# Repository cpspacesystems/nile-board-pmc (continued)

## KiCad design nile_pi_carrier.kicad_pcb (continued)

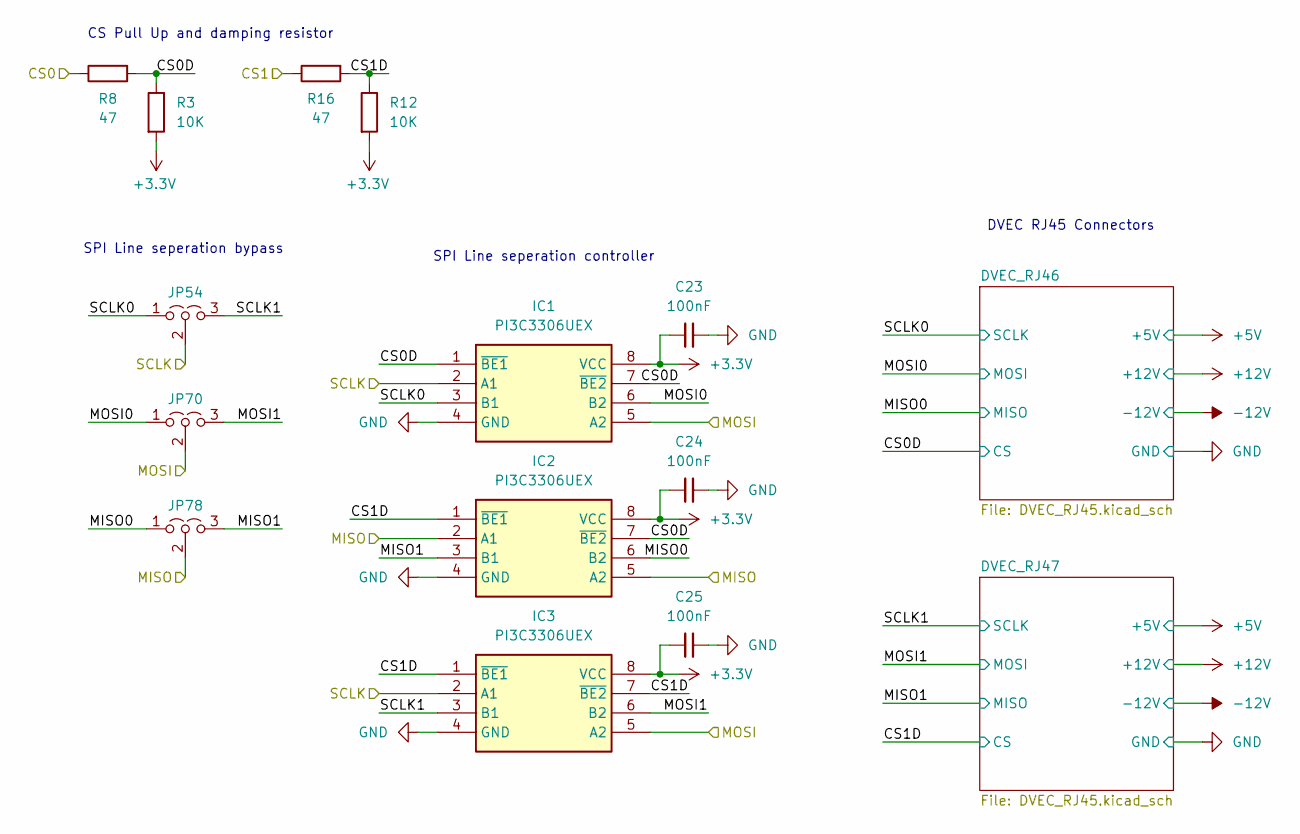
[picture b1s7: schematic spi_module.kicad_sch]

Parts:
C23, C24, C25: 100nF; C_0402_1005Metric
IC1, IC2, IC3: PI3C3306UEX; SOP65P490X110-8N; Manufacturer_Part_Number PI3C3306UEX; Mouser Part Number 729-PI3C3306UEX
JP54, JP70, JP78: SPI Iso Bypass; SolderJumper-3_P1.3mm_Open_Pad1.0x1.5mm_NumberLabels
R3, R12: 10K; R_0402_1005Metric_Pad0.72x0.64mm_HandSolder
R8, R16: 47; R_0402_1005Metric_Pad0.72x0.64mm_HandSolder

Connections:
+3.3V: C23.1, C24.1, C25.1, IC1.8 (VCC), IC2.8 (VCC), IC3.8 (VCC), R3.2, R12.2; also elsewhere on the board
/CS0: R8.1; also elsewhere on the board
/CS1: R16.1; also elsewhere on the board
/spi_bank/MISOA: IC2.2 (A1), IC2.5 (A2), JP78.2 (C); also elsewhere on the board
/spi_bank/MOSIA: IC1.5 (A2), IC3.5 (A2), JP70.2 (C); also elsewhere on the board
/spi_bank/SCLKA: IC1.2 (A1), IC3.2 (A1), JP54.2 (C); also elsewhere on the board
/spi_bank/SPI Module/CS0D: IC1.1 (~BE1), IC1.7 (~BE2), IC2.7 (~BE2), R3.1, R8.2; also elsewhere on the board
/spi_bank/SPI Module/CS1D: IC2.1 (~BE1), IC3.1 (~BE1), IC3.7 (~BE2), R12.1, R16.2; also elsewhere on the board
/spi_bank/SPI Module/MISO0: IC2.6 (B2), JP78.1 (A); also elsewhere on the board
/spi_bank/SPI Module/MISO1: IC2.3 (B1), JP78.3 (B); also elsewhere on the board
/spi_bank/SPI Module/MOSI0: IC1.6 (B2), JP70.1 (A); also elsewhere on the board
/spi_bank/SPI Module/MOSI1: IC3.6 (B2), JP70.3 (B); also elsewhere on the board
/spi_bank/SPI Module/SCLK0: IC1.3 (B1), JP54.1 (A); also elsewhere on the board
/spi_bank/SPI Module/SCLK1: IC3.3 (B1), JP54.3 (B); also elsewhere on the board
GND: C23.2, C24.2, C25.2, IC1.4 (GND), IC2.4 (GND), IC3.4 (GND); also elsewhere on the board

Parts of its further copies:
C26, C27, C28, C29, C30, C31, C32, C33, C34, C35, C36, C37, C38, C39, C40, C41, C42, C43, C44, C45, C46: 100nF; C_0402_1005Metric
IC4, IC5, IC6, IC7, IC8, IC9, IC10, IC11, IC12, IC13, IC14, IC15, IC16, IC17, IC18, IC19, IC20, IC21, IC22, IC23, IC24: PI3C3306UEX; SOP65P490X110-8N; Manufacturer_Part_Number PI3C3306UEX; Mouser Part Number 729-PI3C3306UEX
JP55, JP56, JP57, JP58, JP59, JP60, JP61, JP71, JP72, JP73, JP74, JP75, JP76, JP77, JP79, JP80, JP81, JP82, JP83, JP84, JP85: SPI Iso Bypass; SolderJumper-3_P1.3mm_Open_Pad1.0x1.5mm_NumberLabels
R40, R48, R56, R60, R68, R76, R80, R88, R96, R145, R147, R149, R151, R153: 10K; R_0402_1005Metric_Pad0.72x0.64mm_HandSolder
R44, R52, R57, R64, R72, R77, R84, R92, R144, R146, R148, R150, R152, R154: 47; R_0402_1005Metric_Pad0.72x0.64mm_HandSolder

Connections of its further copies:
+3.3V: C26.1, C27.1, C28.1, C29.1, C30.1, C31.1, C32.1, C33.1, C34.1, C35.1, C36.1, C37.1, C38.1, C39.1, C40.1, C41.1, C42.1, C43.1, C44.1, C45.1, C46.1, IC4.8 (VCC), IC5.8 (VCC), IC6.8 (VCC), IC7.8 (VCC), IC8.8 (VCC), IC9.8 (VCC), IC10.8 (VCC), IC11.8 (VCC), IC12.8 (VCC), IC13.8 (VCC), IC14.8 (VCC), IC15.8 (VCC), IC16.8 (VCC), IC17.8 (VCC), IC18.8 (VCC), IC19.8 (VCC), IC20.8 (VCC), IC21.8 (VCC), IC22.8 (VCC), IC23.8 (VCC), IC24.8 (VCC), R40.2, R48.2, R56.2, R60.2, R68.2, R76.2, R80.2, R88.2, R96.2, R145.2, R147.2, R149.2, R151.2, R153.2; also elsewhere on the board
/CS2: R44.1; also elsewhere on the board
/CS3: R52.1; also elsewhere on the board
/CS4: R57.1; also elsewhere on the board
/CS5: R64.1; also elsewhere on the board
/CS6: R72.1; also elsewhere on the board
/CS7: R77.1; also elsewhere on the board
/CS8: R84.1; also elsewhere on the board
/CS9: R92.1; also elsewhere on the board
/CS10: R144.1; also elsewhere on the board
/CS11: R146.1; also elsewhere on the board
/CS12: R148.1; also elsewhere on the board
/CS13: R150.1; also elsewhere on the board
/CS14: R152.1; also elsewhere on the board
/CS15: R154.1; also elsewhere on the board
/spi_bank/MISOA: IC5.2 (A1), IC5.5 (A2), IC8.2 (A1), IC8.5 (A2), IC11.2 (A1), IC11.5 (A2), JP79.2 (C), JP80.2 (C), JP81.2 (C); also elsewhere on the board
/spi_bank/MISOB: IC14.2 (A1), IC14.5 (A2), IC17.2 (A1), IC17.5 (A2), IC20.2 (A1), IC20.5 (A2), IC23.2 (A1), IC23.5 (A2), JP82.2 (C), JP83.2 (C), JP84.2 (C), JP85.2 (C); also elsewhere on the board
/spi_bank/MOSIA: IC4.5 (A2), IC6.5 (A2), IC7.5 (A2), IC9.5 (A2), IC10.5 (A2), IC12.5 (A2), JP71.2 (C), JP72.2 (C), JP73.2 (C); also elsewhere on the board
/spi_bank/MOSIB: IC13.5 (A2), IC15.5 (A2), IC16.5 (A2), IC18.5 (A2), IC19.5 (A2), IC21.5 (A2), IC22.5 (A2), IC24.5 (A2), JP74.2 (C), JP75.2 (C), JP76.2 (C), JP77.2 (C); also elsewhere on the board
/spi_bank/SCLKA: IC4.2 (A1), IC6.2 (A1), IC7.2 (A1), IC9.2 (A1), IC10.2 (A1), IC12.2 (A1), JP55.2 (C), JP56.2 (C), JP57.2 (C); also elsewhere on the board
/spi_bank/SCLKB: IC13.2 (A1), IC15.2 (A1), IC16.2 (A1), IC18.2 (A1), IC19.2 (A1), IC21.2 (A1), IC22.2 (A1), IC24.2 (A1), JP58.2 (C), JP59.2 (C), JP60.2 (C), JP61.2 (C); also elsewhere on the board
/spi_bank/SPI Module1/CS0D: IC4.1 (~BE1), IC4.7 (~BE2), IC5.7 (~BE2), R40.1, R44.2; also elsewhere on the board
/spi_bank/SPI Module1/CS1D: IC5.1 (~BE1), IC6.1 (~BE1), IC6.7 (~BE2), R48.1, R52.2; also elsewhere on the board
/spi_bank/SPI Module1/MISO0: IC5.6 (B2), JP79.1 (A); also elsewhere on the board
/spi_bank/SPI Module1/MISO1: IC5.3 (B1), JP79.3 (B); also elsewhere on the board
/spi_bank/SPI Module1/MOSI0: IC4.6 (B2), JP71.1 (A); also elsewhere on the board
/spi_bank/SPI Module1/MOSI1: IC6.6 (B2), JP71.3 (B); also elsewhere on the board
/spi_bank/SPI Module1/SCLK0: IC4.3 (B1), JP55.1 (A); also elsewhere on the board
/spi_bank/SPI Module1/SCLK1: IC6.3 (B1), JP55.3 (B); also elsewhere on the board
/spi_bank/SPI Module2/CS0D: IC7.1 (~BE1), IC7.7 (~BE2), IC8.7 (~BE2), R56.1, R57.2; also elsewhere on the board
/spi_bank/SPI Module2/CS1D: IC8.1 (~BE1), IC9.1 (~BE1), IC9.7 (~BE2), R60.1, R64.2; also elsewhere on the board
/spi_bank/SPI Module2/MISO0: IC8.6 (B2), JP80.1 (A); also elsewhere on the board
/spi_bank/SPI Module2/MISO1: IC8.3 (B1), JP80.3 (B); also elsewhere on the board
/spi_bank/SPI Module2/MOSI0: IC7.6 (B2), JP72.1 (A); also elsewhere on the board
/spi_bank/SPI Module2/MOSI1: IC9.6 (B2), JP72.3 (B); also elsewhere on the board
/spi_bank/SPI Module2/SCLK0: IC7.3 (B1), JP56.1 (A); also elsewhere on the board
/spi_bank/SPI Module2/SCLK1: IC9.3 (B1), JP56.3 (B); also elsewhere on the board
/spi_bank/SPI Module3/CS0D: IC10.1 (~BE1), IC10.7 (~BE2), IC11.7 (~BE2), R68.1, R72.2; also elsewhere on the board
/spi_bank/SPI Module3/CS1D: IC11.1 (~BE1), IC12.1 (~BE1), IC12.7 (~BE2), R76.1, R77.2; also elsewhere on the board
/spi_bank/SPI Module3/MISO0: IC11.6 (B2), JP81.1 (A); also elsewhere on the board
/spi_bank/SPI Module3/MISO1: IC11.3 (B1), JP81.3 (B); also elsewhere on the board
/spi_bank/SPI Module3/MOSI0: IC10.6 (B2), JP73.1 (A); also elsewhere on the board
/spi_bank/SPI Module3/MOSI1: IC12.6 (B2), JP73.3 (B); also elsewhere on the board
/spi_bank/SPI Module3/SCLK0: IC10.3 (B1), JP57.1 (A); also elsewhere on the board
/spi_bank/SPI Module3/SCLK1: IC12.3 (B1), JP57.3 (B); also elsewhere on the board
/spi_bank/SPI Module4/CS0D: IC13.1 (~BE1), IC13.7 (~BE2), IC14.7 (~BE2), R80.1, R84.2; also elsewhere on the board
/spi_bank/SPI Module4/CS1D: IC14.1 (~BE1), IC15.1 (~BE1), IC15.7 (~BE2), R88.1, R92.2; also elsewhere on the board
/spi_bank/SPI Module4/MISO0: IC14.6 (B2), JP82.1 (A); also elsewhere on the board
/spi_bank/SPI Module4/MISO1: IC14.3 (B1), JP82.3 (B); also elsewhere on the board
/spi_bank/SPI Module4/MOSI0: IC13.6 (B2), JP74.1 (A); also elsewhere on the board
/spi_bank/SPI Module4/MOSI1: IC15.6 (B2), JP74.3 (B); also elsewhere on the board
/spi_bank/SPI Module4/SCLK0: IC13.3 (B1), JP58.1 (A); also elsewhere on the board
/spi_bank/SPI Module4/SCLK1: IC15.3 (B1), JP58.3 (B); also elsewhere on the board
/spi_bank/SPI Module5/CS0D: IC16.1 (~BE1), IC16.7 (~BE2), IC17.7 (~BE2), R96.1, R144.2; also elsewhere on the board
/spi_bank/SPI Module5/CS1D: IC17.1 (~BE1), IC18.1 (~BE1), IC18.7 (~BE2), R145.1, R146.2; also elsewhere on the board
/spi_bank/SPI Module5/MISO0: IC17.6 (B2), JP83.1 (A); also elsewhere on the board
/spi_bank/SPI Module5/MISO1: IC17.3 (B1), JP83.3 (B); also elsewhere on the board
/spi_bank/SPI Module5/MOSI0: IC16.6 (B2), JP75.1 (A); also elsewhere on the board
/spi_bank/SPI Module5/MOSI1: IC18.6 (B2), JP75.3 (B); also elsewhere on the board
/spi_bank/SPI Module5/SCLK0: IC16.3 (B1), JP59.1 (A); also elsewhere on the board
/spi_bank/SPI Module5/SCLK1: IC18.3 (B1), JP59.3 (B); also elsewhere on the board
/spi_bank/SPI Module6/CS0D: IC19.1 (~BE1), IC19.7 (~BE2), IC20.7 (~BE2), R147.1, R148.2; also elsewhere on the board
/spi_bank/SPI Module6/CS1D: IC20.1 (~BE1), IC21.1 (~BE1), IC21.7 (~BE2), R149.1, R150.2; also elsewhere on the board
/spi_bank/SPI Module6/MISO0: IC20.6 (B2), JP84.1 (A); also elsewhere on the board
/spi_bank/SPI Module6/MISO1: IC20.3 (B1), JP84.3 (B); also elsewhere on the board
/spi_bank/SPI Module6/MOSI0: IC19.6 (B2), JP76.1 (A); also elsewhere on the board
/spi_bank/SPI Module6/MOSI1: IC21.6 (B2), JP76.3 (B); also elsewhere on the board
/spi_bank/SPI Module6/SCLK0: IC19.3 (B1), JP60.1 (A); also elsewhere on the board
/spi_bank/SPI Module6/SCLK1: IC21.3 (B1), JP60.3 (B); also elsewhere on the board
/spi_bank/SPI Module7/CS0D: IC22.1 (~BE1), IC22.7 (~BE2), IC23.7 (~BE2), R151.1, R152.2; also elsewhere on the board
/spi_bank/SPI Module7/CS1D: IC23.1 (~BE1), IC24.1 (~BE1), IC24.7 (~BE2), R153.1, R154.2; also elsewhere on the board
/spi_bank/SPI Module7/MISO0: IC23.6 (B2), JP85.1 (A); also elsewhere on the board
/spi_bank/SPI Module7/MISO1: IC23.3 (B1), JP85.3 (B); also elsewhere on the board
/spi_bank/SPI Module7/MOSI0: IC22.6 (B2), JP77.1 (A); also elsewhere on the board
/spi_bank/SPI Module7/MOSI1: IC24.6 (B2), JP77.3 (B); also elsewhere on the board
/spi_bank/SPI Module7/SCLK0: IC22.3 (B1), JP61.1 (A); also elsewhere on the board
/spi_bank/SPI Module7/SCLK1: IC24.3 (B1), JP61.3 (B); also elsewhere on the board
GND: C26.2, C27.2, C28.2, C29.2, C30.2, C31.2, C32.2, C33.2, C34.2, C35.2, C36.2, C37.2, C38.2, C39.2, C40.2, C41.2, C42.2, C43.2, C44.2, C45.2, C46.2, IC4.4 (GND), IC5.4 (GND), IC6.4 (GND), IC7.4 (GND), IC8.4 (GND), IC9.4 (GND), IC10.4 (GND), IC11.4 (GND), IC12.4 (GND), IC13.4 (GND), IC14.4 (GND), IC15.4 (GND), IC16.4 (GND), IC17.4 (GND), IC18.4 (GND), IC19.4 (GND), IC20.4 (GND), IC21.4 (GND), IC22.4 (GND), IC23.4 (GND), IC24.4 (GND); also elsewhere on the board

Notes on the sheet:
DVEC RJ45 Connectors
SPI Line seperation bypass
SPI Line seperation controller
CS Pull Up and damping resistor

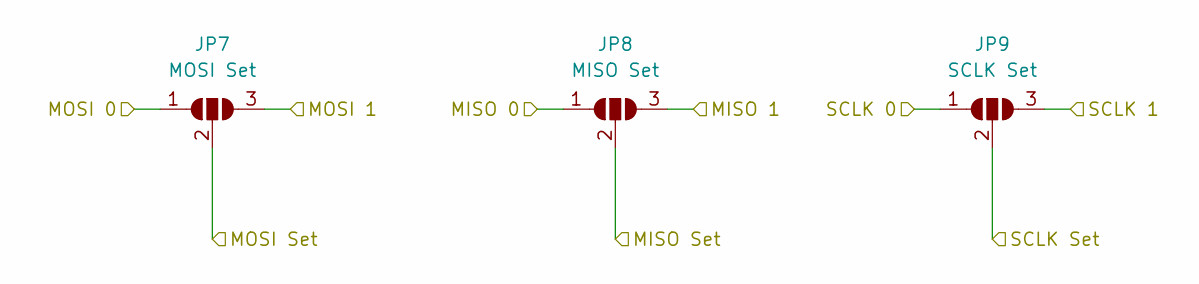
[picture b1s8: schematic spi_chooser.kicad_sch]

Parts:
JP7: MOSI Set; SolderJumper-3_P1.3mm_Open_Pad1.0x1.5mm_NumberLabels
JP8: MISO Set; SolderJumper-3_P1.3mm_Open_Pad1.0x1.5mm_NumberLabels
JP9: SCLK Set; SolderJumper-3_P1.3mm_Open_Pad1.0x1.5mm_NumberLabels

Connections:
/spi_bank/MISOA: JP8.2 (C); also elsewhere on the board
/spi_bank/MISOD0: JP8.1 (A); also elsewhere on the board
/spi_bank/MISOD1: JP8.3 (B); also elsewhere on the board
/spi_bank/MOSIA: JP7.2 (C); also elsewhere on the board
/spi_bank/MOSID0: JP7.1 (A); also elsewhere on the board
/spi_bank/MOSID1: JP7.3 (B); also elsewhere on the board
/spi_bank/SCLKA: JP9.2 (C); also elsewhere on the board
/spi_bank/SCLKD0: JP9.1 (A); also elsewhere on the board
/spi_bank/SCLKD1: JP9.3 (B); also elsewhere on the board

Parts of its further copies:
JP10: MOSI Set; SolderJumper-3_P1.3mm_Open_Pad1.0x1.5mm_NumberLabels
JP11: MISO Set; SolderJumper-3_P1.3mm_Open_Pad1.0x1.5mm_NumberLabels
JP12: SCLK Set; SolderJumper-3_P1.3mm_Open_Pad1.0x1.5mm_NumberLabels

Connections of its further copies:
/spi_bank/MISOB: JP11.2 (C); also elsewhere on the board
/spi_bank/MISOD0: JP11.1 (A); also elsewhere on the board
/spi_bank/MISOD1: JP11.3 (B); also elsewhere on the board
/spi_bank/MOSIB: JP10.2 (C); also elsewhere on the board
/spi_bank/MOSID0: JP10.1 (A); also elsewhere on the board
/spi_bank/MOSID1: JP10.3 (B); also elsewhere on the board
/spi_bank/SCLKB: JP12.2 (C); also elsewhere on the board
/spi_bank/SCLKD0: JP12.1 (A); also elsewhere on the board
/spi_bank/SCLKD1: JP12.3 (B); also elsewhere on the board

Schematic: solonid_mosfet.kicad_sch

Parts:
D1: SMF28A; D_SOD-123F
D25: LED; D_0603_1608Metric_Pad1.05x0.95mm_HandSolder
F2: PF 100mA; Fuse_1206_3216Metric_Pad1.42x1.75mm_HandSolder
Q1: BSS84; SOT-23
Q2: 2SK3018; SOT-323_SC-70
R1, R155: 27K; R_0402_1005Metric_Pad0.72x0.64mm_HandSolder
R2: 280; R_0402_1005Metric_Pad0.72x0.64mm_HandSolder
R85: 5.1K; R_0805_2012Metric_Pad1.20x1.40mm_HandSolder
R120: 10K; R_0402_1005Metric_Pad0.72x0.64mm_HandSolder

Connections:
/Solonid Bank Controller/DSUB 1: D1.1 (A1), F2.2, R85.1; also elsewhere on the board
/Solonid Bank Controller/S1 A: R2.2, R120.2; also elsewhere on the board
GND: D1.2 (A2), D25.1 (K), Q2.2 (S), R120.1; also elsewhere on the board
unnamed: D25.2 (A), R85.2
unnamed: F2.1, Q1.3 (D)
unnamed: Q1.1 (G), R1.2, R155.1
unnamed: Q2.3 (D), R155.2
unnamed: Q2.1 (G), R2.1
VBUS: Q1.2 (S), R1.1; also elsewhere on the board

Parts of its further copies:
D2, D3, D4, D5, D6, D7, D8, D9, D10, D11, D12, D13, D14, D15, D16, D17, D18, D19, D20, D21, D22, D23, D24: SMF28A; D_SOD-123F
D26, D27, D28, D29, D30, D31, D32, D33, D34, D35, D36, D37, D38, D39, D40, D41, D42, D43, D44, D45, D46, D47, D48: LED; D_0603_1608Metric_Pad1.05x0.95mm_HandSolder
F3, F4, F5, F6, F7, F8, F9, F10, F11, F12, F13, F14, F15, F16, F17, F18, F19, F20, F21, F22, F23, F24, F25: PF 100mA; Fuse_1206_3216Metric_Pad1.42x1.75mm_HandSolder
Q3, Q5, Q7, Q9, Q11, Q13, Q15, Q17, Q19, Q21, Q23, Q25, Q27, Q29, Q31, Q33, Q35, Q37, Q39, Q41, Q43, Q45, Q47: 2SK3018; SOT-323_SC-70
Q4, Q6, Q8, Q10, Q12, Q14, Q16, Q18, Q20, Q22, Q24, Q26, Q28, Q30, Q32, Q34, Q36, Q38, Q40, Q42, Q44, Q46, Q48: BSS84; SOT-23
R6, R10, R14, R18, R22, R26, R30, R34, R38, R42, R46, R50, R54, R58, R62, R66, R70, R74, R78, R82, R86, R90, R94: 280; R_0402_1005Metric_Pad0.72x0.64mm_HandSolder
R7, R11, R15, R19, R23, R27, R31, R35, R39, R43, R47, R51, R55, R59, R63, R67, R71, R75, R79, R83, R87, R91, R95, R156, R157, R158, R159, R161, R162, R163, R164, R165, R166, R167, R168, R169, R170, R171, R172, R173, R174, R175, R176, R177, R178, R179: 27K; R_0402_1005Metric_Pad0.72x0.64mm_HandSolder
R89, R93, R99, R100, R101, R102, R103, R104, R105, R106, R107, R108, R109, R110, R111, R112, R113, R114, R115, R116, R117, R118, R119: 5.1K; R_0805_2012Metric_Pad1.20x1.40mm_HandSolder
R121, R122, R123, R124, R125, R126, R127, R128, R129, R130, R131, R132, R133, R134, R135, R136, R137, R138, R139, R140, R141, R142, R143: 10K; R_0402_1005Metric_Pad0.72x0.64mm_HandSolder

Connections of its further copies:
/Solonid Bank Controller/DSUB 2: D3.1 (A1), F4.2, R93.1; also elsewhere on the board
/Solonid Bank Controller/DSUB 3: D5.1 (A1), F6.2, R100.1; also elsewhere on the board
/Solonid Bank Controller/DSUB 4: D7.1 (A1), F8.2, R102.1; also elsewhere on the board
/Solonid Bank Controller/DSUB 5: D9.1 (A1), F10.2, R104.1; also elsewhere on the board
/Solonid Bank Controller/DSUB 6: D11.1 (A1), F12.2, R106.1; also elsewhere on the board
/Solonid Bank Controller/DSUB 7: D13.1 (A1), F14.2, R108.1; also elsewhere on the board
/Solonid Bank Controller/DSUB 8: D15.1 (A1), F16.2, R110.1; also elsewhere on the board
/Solonid Bank Controller/DSUB 9: D17.1 (A1), F18.2, R112.1; also elsewhere on the board
/Solonid Bank Controller/DSUB 10: D19.1 (A1), F20.2, R114.1; also elsewhere on the board
/Solonid Bank Controller/DSUB 11: D21.1 (A1), F22.2, R116.1; also elsewhere on the board
/Solonid Bank Controller/DSUB 12: D23.1 (A1), F24.2, R118.1; also elsewhere on the board
/Solonid Bank Controller/DSUB 14: D2.1 (A1), F3.2, R89.1; also elsewhere on the board
/Solonid Bank Controller/DSUB 15: D4.1 (A1), F5.2, R99.1; also elsewhere on the board
/Solonid Bank Controller/DSUB 16: D6.1 (A1), F7.2, R101.1; also elsewhere on the board
/Solonid Bank Controller/DSUB 17: D8.1 (A1), F9.2, R103.1; also elsewhere on the board
/Solonid Bank Controller/DSUB 18: D10.1 (A1), F11.2, R105.1; also elsewhere on the board
/Solonid Bank Controller/DSUB 19: D12.1 (A1), F13.2, R107.1; also elsewhere on the board
/Solonid Bank Controller/DSUB 20: D14.1 (A1), F15.2, R109.1; also elsewhere on the board
/Solonid Bank Controller/DSUB 21: D16.1 (A1), F17.2, R111.1; also elsewhere on the board
/Solonid Bank Controller/DSUB 22: D18.1 (A1), F19.2, R113.1; also elsewhere on the board
/Solonid Bank Controller/DSUB 23: D20.1 (A1), F21.2, R115.1; also elsewhere on the board
/Solonid Bank Controller/DSUB 24: D22.1 (A1), F23.2, R117.1; also elsewhere on the board
/Solonid Bank Controller/DSUB 25: D24.1 (A1), F25.2, R119.1; also elsewhere on the board
/Solonid Bank Controller/S1 B: R6.2, R121.2; also elsewhere on the board
/Solonid Bank Controller/S2 A: R10.2, R122.2; also elsewhere on the board
/Solonid Bank Controller/S2 B: R14.2, R123.2; also elsewhere on the board
/Solonid Bank Controller/S3 A: R18.2, R124.2; also elsewhere on the board
/Solonid Bank Controller/S3 B: R22.2, R125.2; also elsewhere on the board
/Solonid Bank Controller/S4 A: R26.2, R126.2; also elsewhere on the board
/Solonid Bank Controller/S4 B: R30.2, R127.2; also elsewhere on the board
/Solonid Bank Controller/S5 A: R34.2, R128.2; also elsewhere on the board
/Solonid Bank Controller/S5 B: R38.2, R129.2; also elsewhere on the board
/Solonid Bank Controller/S6 A: R42.2, R130.2; also elsewhere on the board
/Solonid Bank Controller/S6 B: R46.2, R131.2; also elsewhere on the board
/Solonid Bank Controller/S7 A: R50.2, R132.2; also elsewhere on the board
/Solonid Bank Controller/S7 B: R54.2, R133.2; also elsewhere on the board
/Solonid Bank Controller/S8 A: R58.2, R134.2; also elsewhere on the board
/Solonid Bank Controller/S8 B: R62.2, R135.2; also elsewhere on the board
/Solonid Bank Controller/S9 A: R66.2, R136.2; also elsewhere on the board
/Solonid Bank Controller/S9 B: R70.2, R137.2; also elsewhere on the board
/Solonid Bank Controller/S10 A: R74.2, R138.2; also elsewhere on the board
/Solonid Bank Controller/S10 B: R78.2, R139.2; also elsewhere on the board
/Solonid Bank Controller/S11 A: R82.2, R140.2; also elsewhere on the board
/Solonid Bank Controller/S11 B: R86.2, R141.2; also elsewhere on the board
/Solonid Bank Controller/S12 A: R90.2, R142.2; also elsewhere on the board
/Solonid Bank Controller/S12 B: R94.2, R143.2; also elsewhere on the board
GND: D2.2 (A2), D3.2 (A2), D4.2 (A2), D5.2 (A2), D6.2 (A2), D7.2 (A2), D8.2 (A2), D9.2 (A2), D10.2 (A2), D11.2 (A2), D12.2 (A2), D13.2 (A2), D14.2 (A2), D15.2 (A2), D16.2 (A2), D17.2 (A2), D18.2 (A2), D19.2 (A2), D20.2 (A2), D21.2 (A2), D22.2 (A2), D23.2 (A2), D24.2 (A2), D26.1 (K), D27.1 (K), D28.1 (K), D29.1 (K), D30.1 (K), D31.1 (K), D32.1 (K), D33.1 (K), D34.1 (K), D35.1 (K), D36.1 (K), D37.1 (K), D38.1 (K), D39.1 (K), D40.1 (K), D41.1 (K), D42.1 (K), D43.1 (K), D44.1 (K), D45.1 (K), D46.1 (K), D47.1 (K), D48.1 (K), Q3.2 (S), Q5.2 (S), Q7.2 (S), Q9.2 (S), Q11.2 (S), Q13.2 (S), Q15.2 (S), Q17.2 (S), Q19.2 (S), Q21.2 (S), Q23.2 (S), Q25.2 (S), Q27.2 (S), Q29.2 (S), Q31.2 (S), Q33.2 (S), Q35.2 (S), Q37.2 (S), Q39.2 (S), Q41.2 (S), Q43.2 (S), Q45.2 (S), Q47.2 (S), R121.1, R122.1, R123.1, R124.1, R125.1, R126.1, R127.1, R128.1, R129.1, R130.1, R131.1, R132.1, R133.1, R134.1, R135.1, R136.1, R137.1, R138.1, R139.1, R140.1, R141.1, R142.1, R143.1; also elsewhere on the board
unnamed: D26.2 (A), R89.2
unnamed: D27.2 (A), R93.2
unnamed: D28.2 (A), R99.2
unnamed: D29.2 (A), R100.2
unnamed: D30.2 (A), R101.2
unnamed: D31.2 (A), R102.2
unnamed: D32.2 (A), R103.2
unnamed: D33.2 (A), R104.2
unnamed: D34.2 (A), R105.2
unnamed: D35.2 (A), R106.2
unnamed: D36.2 (A), R107.2
unnamed: D37.2 (A), R108.2
unnamed: D38.2 (A), R109.2
unnamed: D39.2 (A), R110.2
unnamed: D40.2 (A), R111.2
unnamed: D41.2 (A), R112.2
unnamed: D42.2 (A), R113.2
unnamed: D43.2 (A), R114.2
unnamed: D44.2 (A), R115.2
unnamed: D45.2 (A), R116.2
unnamed: D46.2 (A), R117.2
unnamed: D47.2 (A), R118.2
unnamed: D48.2 (A), R119.2
unnamed: Q3.3 (D), R156.2
unnamed: Q3.1 (G), R6.1
unnamed: F3.1, Q4.3 (D)
unnamed: Q4.1 (G), R7.2, R156.1
unnamed: Q5.3 (D), R157.2
unnamed: Q5.1 (G), R10.1
unnamed: F4.1, Q6.3 (D)
unnamed: Q6.1 (G), R11.2, R157.1
unnamed: Q7.3 (D), R158.2
unnamed: Q7.1 (G), R14.1
unnamed: F5.1, Q8.3 (D)
unnamed: Q8.1 (G), R15.2, R158.1
unnamed: Q9.3 (D), R159.2
unnamed: Q9.1 (G), R18.1
unnamed: F6.1, Q10.3 (D)
unnamed: Q10.1 (G), R19.2, R159.1
unnamed: Q11.3 (D), R161.2
unnamed: Q11.1 (G), R22.1
unnamed: F7.1, Q12.3 (D)
unnamed: Q12.1 (G), R23.2, R161.1
unnamed: Q13.3 (D), R162.2
unnamed: Q13.1 (G), R26.1
unnamed: F8.1, Q14.3 (D)
unnamed: Q14.1 (G), R27.2, R162.1
unnamed: Q15.3 (D), R163.2
unnamed: Q15.1 (G), R30.1
unnamed: F9.1, Q16.3 (D)
unnamed: Q16.1 (G), R31.2, R163.1
unnamed: Q17.3 (D), R164.2
unnamed: Q17.1 (G), R34.1
unnamed: F10.1, Q18.3 (D)
unnamed: Q18.1 (G), R35.2, R164.1
unnamed: Q19.3 (D), R165.2
unnamed: Q19.1 (G), R38.1
unnamed: F11.1, Q20.3 (D)
unnamed: Q20.1 (G), R39.2, R165.1
unnamed: Q21.3 (D), R166.2
unnamed: Q21.1 (G), R42.1
unnamed: F12.1, Q22.3 (D)
unnamed: Q22.1 (G), R43.2, R166.1
unnamed: Q23.3 (D), R167.2
unnamed: Q23.1 (G), R46.1
unnamed: F13.1, Q24.3 (D)
unnamed: Q24.1 (G), R47.2, R167.1
unnamed: Q25.3 (D), R168.2
unnamed: Q25.1 (G), R50.1
unnamed: F14.1, Q26.3 (D)
unnamed: Q26.1 (G), R51.2, R168.1
unnamed: Q27.3 (D), R169.2
unnamed: Q27.1 (G), R54.1
unnamed: F15.1, Q28.3 (D)
unnamed: Q28.1 (G), R55.2, R169.1
unnamed: Q29.3 (D), R170.2
unnamed: Q29.1 (G), R58.1
unnamed: F16.1, Q30.3 (D)
unnamed: Q30.1 (G), R59.2, R170.1
unnamed: Q31.3 (D), R171.2
unnamed: Q31.1 (G), R62.1
unnamed: F17.1, Q32.3 (D)
unnamed: Q32.1 (G), R63.2, R171.1
unnamed: Q33.3 (D), R172.2
unnamed: Q33.1 (G), R66.1
unnamed: F18.1, Q34.3 (D)
unnamed: Q34.1 (G), R67.2, R172.1
unnamed: Q35.3 (D), R173.2
unnamed: Q35.1 (G), R70.1
unnamed: F19.1, Q36.3 (D)
unnamed: Q36.1 (G), R71.2, R173.1
unnamed: Q37.3 (D), R174.2
unnamed: Q37.1 (G), R74.1
unnamed: F20.1, Q38.3 (D)
unnamed: Q38.1 (G), R75.2, R174.1
unnamed: Q39.3 (D), R175.2
unnamed: Q39.1 (G), R78.1
unnamed: F21.1, Q40.3 (D)
unnamed: Q40.1 (G), R79.2, R175.1
unnamed: Q41.3 (D), R176.2
unnamed: Q41.1 (G), R82.1
unnamed: F22.1, Q42.3 (D)
unnamed: Q42.1 (G), R83.2, R176.1
unnamed: Q43.3 (D), R177.2
unnamed: Q43.1 (G), R86.1
unnamed: F23.1, Q44.3 (D)
unnamed: Q44.1 (G), R87.2, R177.1
unnamed: Q45.3 (D), R178.2
unnamed: Q45.1 (G), R90.1
unnamed: F24.1, Q46.3 (D)
unnamed: Q46.1 (G), R91.2, R178.1
unnamed: Q47.3 (D), R179.2
unnamed: Q47.1 (G), R94.1
unnamed: F25.1, Q48.3 (D)
unnamed: Q48.1 (G), R95.2, R179.1
VBUS: Q4.2 (S), Q6.2 (S), Q8.2 (S), Q10.2 (S), Q12.2 (S), Q14.2 (S), Q16.2 (S), Q18.2 (S), Q20.2 (S), Q22.2 (S), Q24.2 (S), Q26.2 (S), Q28.2 (S), Q30.2 (S), Q32.2 (S), Q34.2 (S), Q36.2 (S), Q38.2 (S), Q40.2 (S), Q42.2 (S), Q44.2 (S), Q46.2 (S), Q48.2 (S), R7.1, R11.1, R15.1, R19.1, R23.1, R27.1, R31.1, R35.1, R39.1, R43.1, R47.1, R51.1, R55.1, R59.1, R63.1, R67.1, R71.1, R75.1, R79.1, R83.1, R87.1, R91.1, R95.1; also elsewhere on the board

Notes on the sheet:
Half of VBUS
Ensure there is a close ground connection to SMF28A To minminize ground loop for return current

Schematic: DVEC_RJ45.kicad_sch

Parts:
J11: RJ45; RJ45-TH_RJ-804-1-6 Yellow

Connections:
+5V: J11.5; also elsewhere on the board
+12V: J11.8; also elsewhere on the board
-12V: J11.7; also elsewhere on the board
/spi_bank/SPI Module/CS0D: J11.2; also elsewhere on the board
/spi_bank/SPI Module/MISO0: J11.6; also elsewhere on the board
/spi_bank/SPI Module/MOSI0: J11.3; also elsewhere on the board
/spi_bank/SPI Module/SCLK0: J11.1; also elsewhere on the board
GND: J11.4; also elsewhere on the board

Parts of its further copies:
J12, J13, J14, J15, J21, J22, J23, J24, J25, J26, J27, J28, J29, J30, J31: RJ45; RJ45-TH_RJ-804-1-6 Yellow

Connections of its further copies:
+5V: J12.5, J13.5, J14.5, J15.5, J21.5, J22.5, J23.5, J24.5, J25.5, J26.5, J27.5, J28.5, J29.5, J30.5, J31.5; also elsewhere on the board
+12V: J12.8, J13.8, J14.8, J15.8, J21.8, J22.8, J23.8, J24.8, J25.8, J26.8, J27.8, J28.8, J29.8, J30.8, J31.8; also elsewhere on the board
-12V: J12.7, J13.7, J14.7, J15.7, J21.7, J22.7, J23.7, J24.7, J25.7, J26.7, J27.7, J28.7, J29.7, J30.7, J31.7; also elsewhere on the board
/spi_bank/SPI Module1/CS0D: J13.2; also elsewhere on the board
/spi_bank/SPI Module1/CS1D: J14.2; also elsewhere on the board
/spi_bank/SPI Module1/MISO0: J13.6; also elsewhere on the board
/spi_bank/SPI Module1/MISO1: J14.6; also elsewhere on the board
/spi_bank/SPI Module1/MOSI0: J13.3; also elsewhere on the board
/spi_bank/SPI Module1/MOSI1: J14.3; also elsewhere on the board
/spi_bank/SPI Module1/SCLK0: J13.1; also elsewhere on the board
/spi_bank/SPI Module1/SCLK1: J14.1; also elsewhere on the board
/spi_bank/SPI Module2/CS0D: J15.2; also elsewhere on the board
/spi_bank/SPI Module2/CS1D: J21.2; also elsewhere on the board
/spi_bank/SPI Module2/MISO0: J15.6; also elsewhere on the board
/spi_bank/SPI Module2/MISO1: J21.6; also elsewhere on the board
/spi_bank/SPI Module2/MOSI0: J15.3; also elsewhere on the board
/spi_bank/SPI Module2/MOSI1: J21.3; also elsewhere on the board
/spi_bank/SPI Module2/SCLK0: J15.1; also elsewhere on the board
/spi_bank/SPI Module2/SCLK1: J21.1; also elsewhere on the board
/spi_bank/SPI Module3/CS0D: J22.2; also elsewhere on the board
/spi_bank/SPI Module3/CS1D: J23.2; also elsewhere on the board
/spi_bank/SPI Module3/MISO0: J22.6; also elsewhere on the board
/spi_bank/SPI Module3/MISO1: J23.6; also elsewhere on the board
/spi_bank/SPI Module3/MOSI0: J22.3; also elsewhere on the board
/spi_bank/SPI Module3/MOSI1: J23.3; also elsewhere on the board
/spi_bank/SPI Module3/SCLK0: J22.1; also elsewhere on the board
/spi_bank/SPI Module3/SCLK1: J23.1; also elsewhere on the board
/spi_bank/SPI Module4/CS0D: J24.2; also elsewhere on the board
/spi_bank/SPI Module4/CS1D: J25.2; also elsewhere on the board
/spi_bank/SPI Module4/MISO0: J24.6; also elsewhere on the board
/spi_bank/SPI Module4/MISO1: J25.6; also elsewhere on the board
/spi_bank/SPI Module4/MOSI0: J24.3; also elsewhere on the board
/spi_bank/SPI Module4/MOSI1: J25.3; also elsewhere on the board
/spi_bank/SPI Module4/SCLK0: J24.1; also elsewhere on the board
/spi_bank/SPI Module4/SCLK1: J25.1; also elsewhere on the board
/spi_bank/SPI Module5/CS0D: J26.2; also elsewhere on the board
/spi_bank/SPI Module5/CS1D: J27.2; also elsewhere on the board
/spi_bank/SPI Module5/MISO0: J26.6; also elsewhere on the board
/spi_bank/SPI Module5/MISO1: J27.6; also elsewhere on the board
/spi_bank/SPI Module5/MOSI0: J26.3; also elsewhere on the board
/spi_bank/SPI Module5/MOSI1: J27.3; also elsewhere on the board
/spi_bank/SPI Module5/SCLK0: J26.1; also elsewhere on the board
/spi_bank/SPI Module5/SCLK1: J27.1; also elsewhere on the board
/spi_bank/SPI Module6/CS0D: J28.2; also elsewhere on the board
/spi_bank/SPI Module6/CS1D: J29.2; also elsewhere on the board
/spi_bank/SPI Module6/MISO0: J28.6; also elsewhere on the board
/spi_bank/SPI Module6/MISO1: J29.6; also elsewhere on the board
/spi_bank/SPI Module6/MOSI0: J28.3; also elsewhere on the board
/spi_bank/SPI Module6/MOSI1: J29.3; also elsewhere on the board
/spi_bank/SPI Module6/SCLK0: J28.1; also elsewhere on the board
/spi_bank/SPI Module6/SCLK1: J29.1; also elsewhere on the board
/spi_bank/SPI Module7/CS0D: J30.2; also elsewhere on the board
/spi_bank/SPI Module7/CS1D: J31.2; also elsewhere on the board
/spi_bank/SPI Module7/MISO0: J30.6; also elsewhere on the board
/spi_bank/SPI Module7/MISO1: J31.6; also elsewhere on the board
/spi_bank/SPI Module7/MOSI0: J30.3; also elsewhere on the board
/spi_bank/SPI Module7/MOSI1: J31.3; also elsewhere on the board
/spi_bank/SPI Module7/SCLK0: J30.1; also elsewhere on the board
/spi_bank/SPI Module7/SCLK1: J31.1; also elsewhere on the board
/spi_bank/SPI Module/CS1D: J12.2; also elsewhere on the board
/spi_bank/SPI Module/MISO1: J12.6; also elsewhere on the board
/spi_bank/SPI Module/MOSI1: J12.3; also elsewhere on the board
/spi_bank/SPI Module/SCLK1: J12.1; also elsewhere on the board
GND: J12.4, J13.4, J14.4, J15.4, J21.4, J22.4, J23.4, J24.4, J25.4, J26.4, J27.4, J28.4, J29.4, J30.4, J31.4; also elsewhere on the board

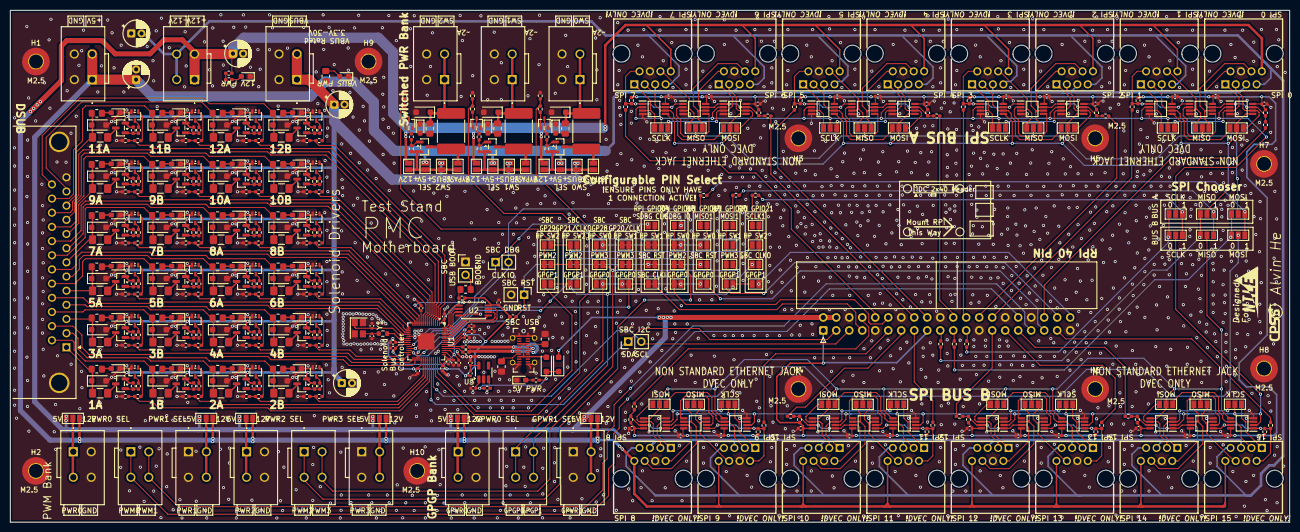
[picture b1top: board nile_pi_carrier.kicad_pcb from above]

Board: 2 copper layers, 250.0 x 100.0 mm, 529 parts (0 on the bottom side), 348 nets.
